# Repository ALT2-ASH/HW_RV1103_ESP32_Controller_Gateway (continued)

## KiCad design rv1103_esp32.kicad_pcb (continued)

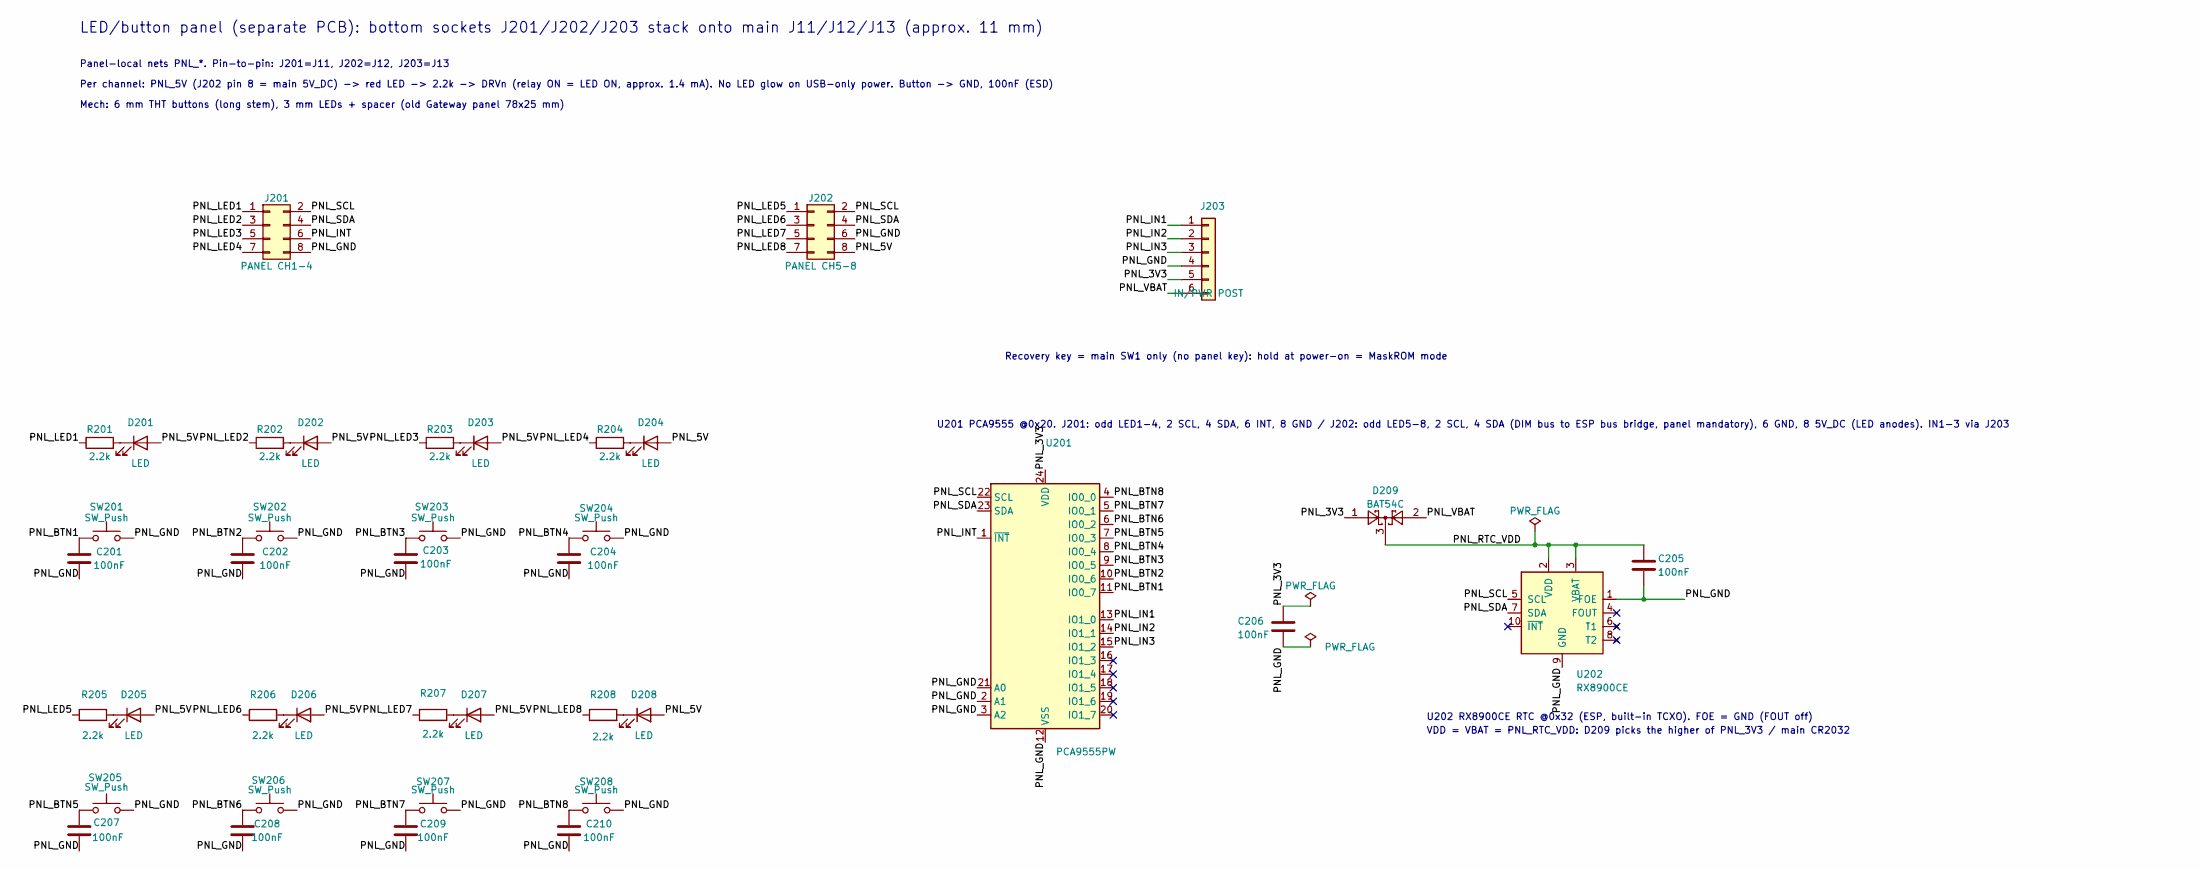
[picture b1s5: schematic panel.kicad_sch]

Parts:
C201, C202, C203, C204, C205, C206, C207, C208, C209, C210: 100nF; C_0603_1608Metric; LCSC C14663
D201, D202, D203, D204, D205, D206, D207, D208: LED; LED_D3.0mm; MPN 204-10SURD/S530-A3-L; LCSC C99771
D209: BAT54C; SOT-23; MPN BAT54C,215; LCSC C37704
J201: PANEL CH1-4; PinSocket_2x04_P2.54mm_Vertical; MPN PM254V-12-08-H85; LCSC C55223345
J202: PANEL CH5-8; PinSocket_2x04_P2.54mm_Vertical; MPN PM254V-12-08-H85; LCSC C55223345
J203: IN/PWR POST; PinSocket_1x06_P2.54mm_Vertical; MPN PM254V-11-06-H85; LCSC C2832269
R201, R202, R203, R204, R205, R206, R207, R208: 2.2k; R_0603_1608Metric; LCSC C4190
SW201, SW202, SW203, SW204, SW205, SW206, SW207, SW208: SW_Push; SW_PUSH_6mm_H8mm; MPN TC-6610-17-260G; LCSC C2845266
U201: PCA9555PW; TSSOP-24_4.4x7.8mm_P0.65mm; MPN PCA9555PW,118; LCSC C128392
U202: RX8900CE; EPSON_CE-USON-10_USON-10_3.2x2.5mm_P0.7mm; MPN RX8900CE-NF; LCSC C54946598

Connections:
/Panel/PNL_3V3: C206.1, D209.1, J203.5, U201.24 (VDD)
/Panel/PNL_5V: D201.2 (A), D202.2 (A), D203.2 (A), D204.2 (A), D205.2 (A), D206.2 (A), D207.2 (A), D208.2 (A), J202.8
/Panel/PNL_BTN1: C201.1, SW201.1, U201.11 (IO0_7)
/Panel/PNL_BTN2: C202.1, SW202.1, U201.10 (IO0_6)
/Panel/PNL_BTN3: C203.1, SW203.1, U201.9 (IO0_5)
/Panel/PNL_BTN4: C204.1, SW204.1, U201.8 (IO0_4)
/Panel/PNL_BTN5: C207.1, SW205.1, U201.7 (IO0_3)
/Panel/PNL_BTN6: C208.1, SW206.1, U201.6 (IO0_2)
/Panel/PNL_BTN7: C209.1, SW207.1, U201.5 (IO0_1)
/Panel/PNL_BTN8: C210.1, SW208.1, U201.4 (IO0_0)
/Panel/PNL_GND: C201.2, C202.2, C203.2, C204.2, C205.2, C206.2, C207.2, C208.2, C209.2, C210.2, J201.8, J202.6, J203.4, SW201.2, SW202.2, SW203.2, SW204.2, SW205.2, SW206.2, SW207.2, SW208.2, U201.2 (A1), U201.3 (A2), U201.12 (VSS), U201.21 (A0), U202.1 (FOE), U202.9 (GND)
/Panel/PNL_IN1: J203.1, U201.13 (IO1_0)
/Panel/PNL_IN2: J203.2, U201.14 (IO1_1)
/Panel/PNL_IN3: J203.3, U201.15 (IO1_2)
/Panel/PNL_INT: J201.6, U201.1 (~INT)
/Panel/PNL_LED1: J201.1, R201.1
/Panel/PNL_LED2: J201.3, R202.1
/Panel/PNL_LED3: J201.5, R203.1
/Panel/PNL_LED4: J201.7, R204.1
/Panel/PNL_LED5: J202.1, R205.1
/Panel/PNL_LED6: J202.3, R206.1
/Panel/PNL_LED7: J202.5, R207.1
/Panel/PNL_LED8: J202.7, R208.1
/Panel/PNL_RTC_VDD: C205.1, D209.3, U202.2 (VDD), U202.3 (VBAT)
/Panel/PNL_SCL: J201.2, J202.2, U201.22 (SCL), U202.5 (SCL)
/Panel/PNL_SDA: J201.4, J202.4, U201.23 (SDA), U202.7 (SDA)
/Panel/PNL_VBAT: D209.2, J203.6
unnamed: D201.1 (K), R201.2
unnamed: D202.1 (K), R202.2
unnamed: D203.1 (K), R203.2
unnamed: D204.1 (K), R204.2
unnamed: D205.1 (K), R205.2
unnamed: D206.1 (K), R206.2
unnamed: D207.1 (K), R207.2
unnamed: D208.1 (K), R208.2

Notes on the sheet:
U202 RX8900CE RTC @0x32 (ESP, built-in TCXO). FOE = GND (FOUT off)
VDD = VBAT = PNL_RTC_VDD: D209 picks the higher of PNL_3V3 / main CR2032
U201 PCA9555 @0x20. J201: odd LED1-4, 2 SCL, 4 SDA, 6 INT, 8 GND / J202: odd LED5-8, 2 SCL, 4 SDA (DIM bus to ESP bus bridge, panel mandatory), 6 GND, 8 5V_DC (LED anodes). IN1-3 via J203
Mech: 6 mm THT buttons (long stem), 3 mm LEDs + spacer (old Gateway panel 78x25 mm)
LED/button panel (separate PCB): bottom sockets J201/J202/J203 stack onto main J11/J12/J13 (approx. 11 mm)
Recovery key = main SW1 only (no panel key): hold at power-on = MaskROM mode
Panel-local nets PNL_*. Pin-to-pin: J201=J11, J202=J12, J203=J13
Per channel: PNL_5V (J202 pin 8 = main 5V_DC) -> red LED -> 2.2k -> DRVn (relay ON = LED ON, approx. 1.4 mA). No LED glow on USB-only power. Button -> GND, 100nF (ESD)

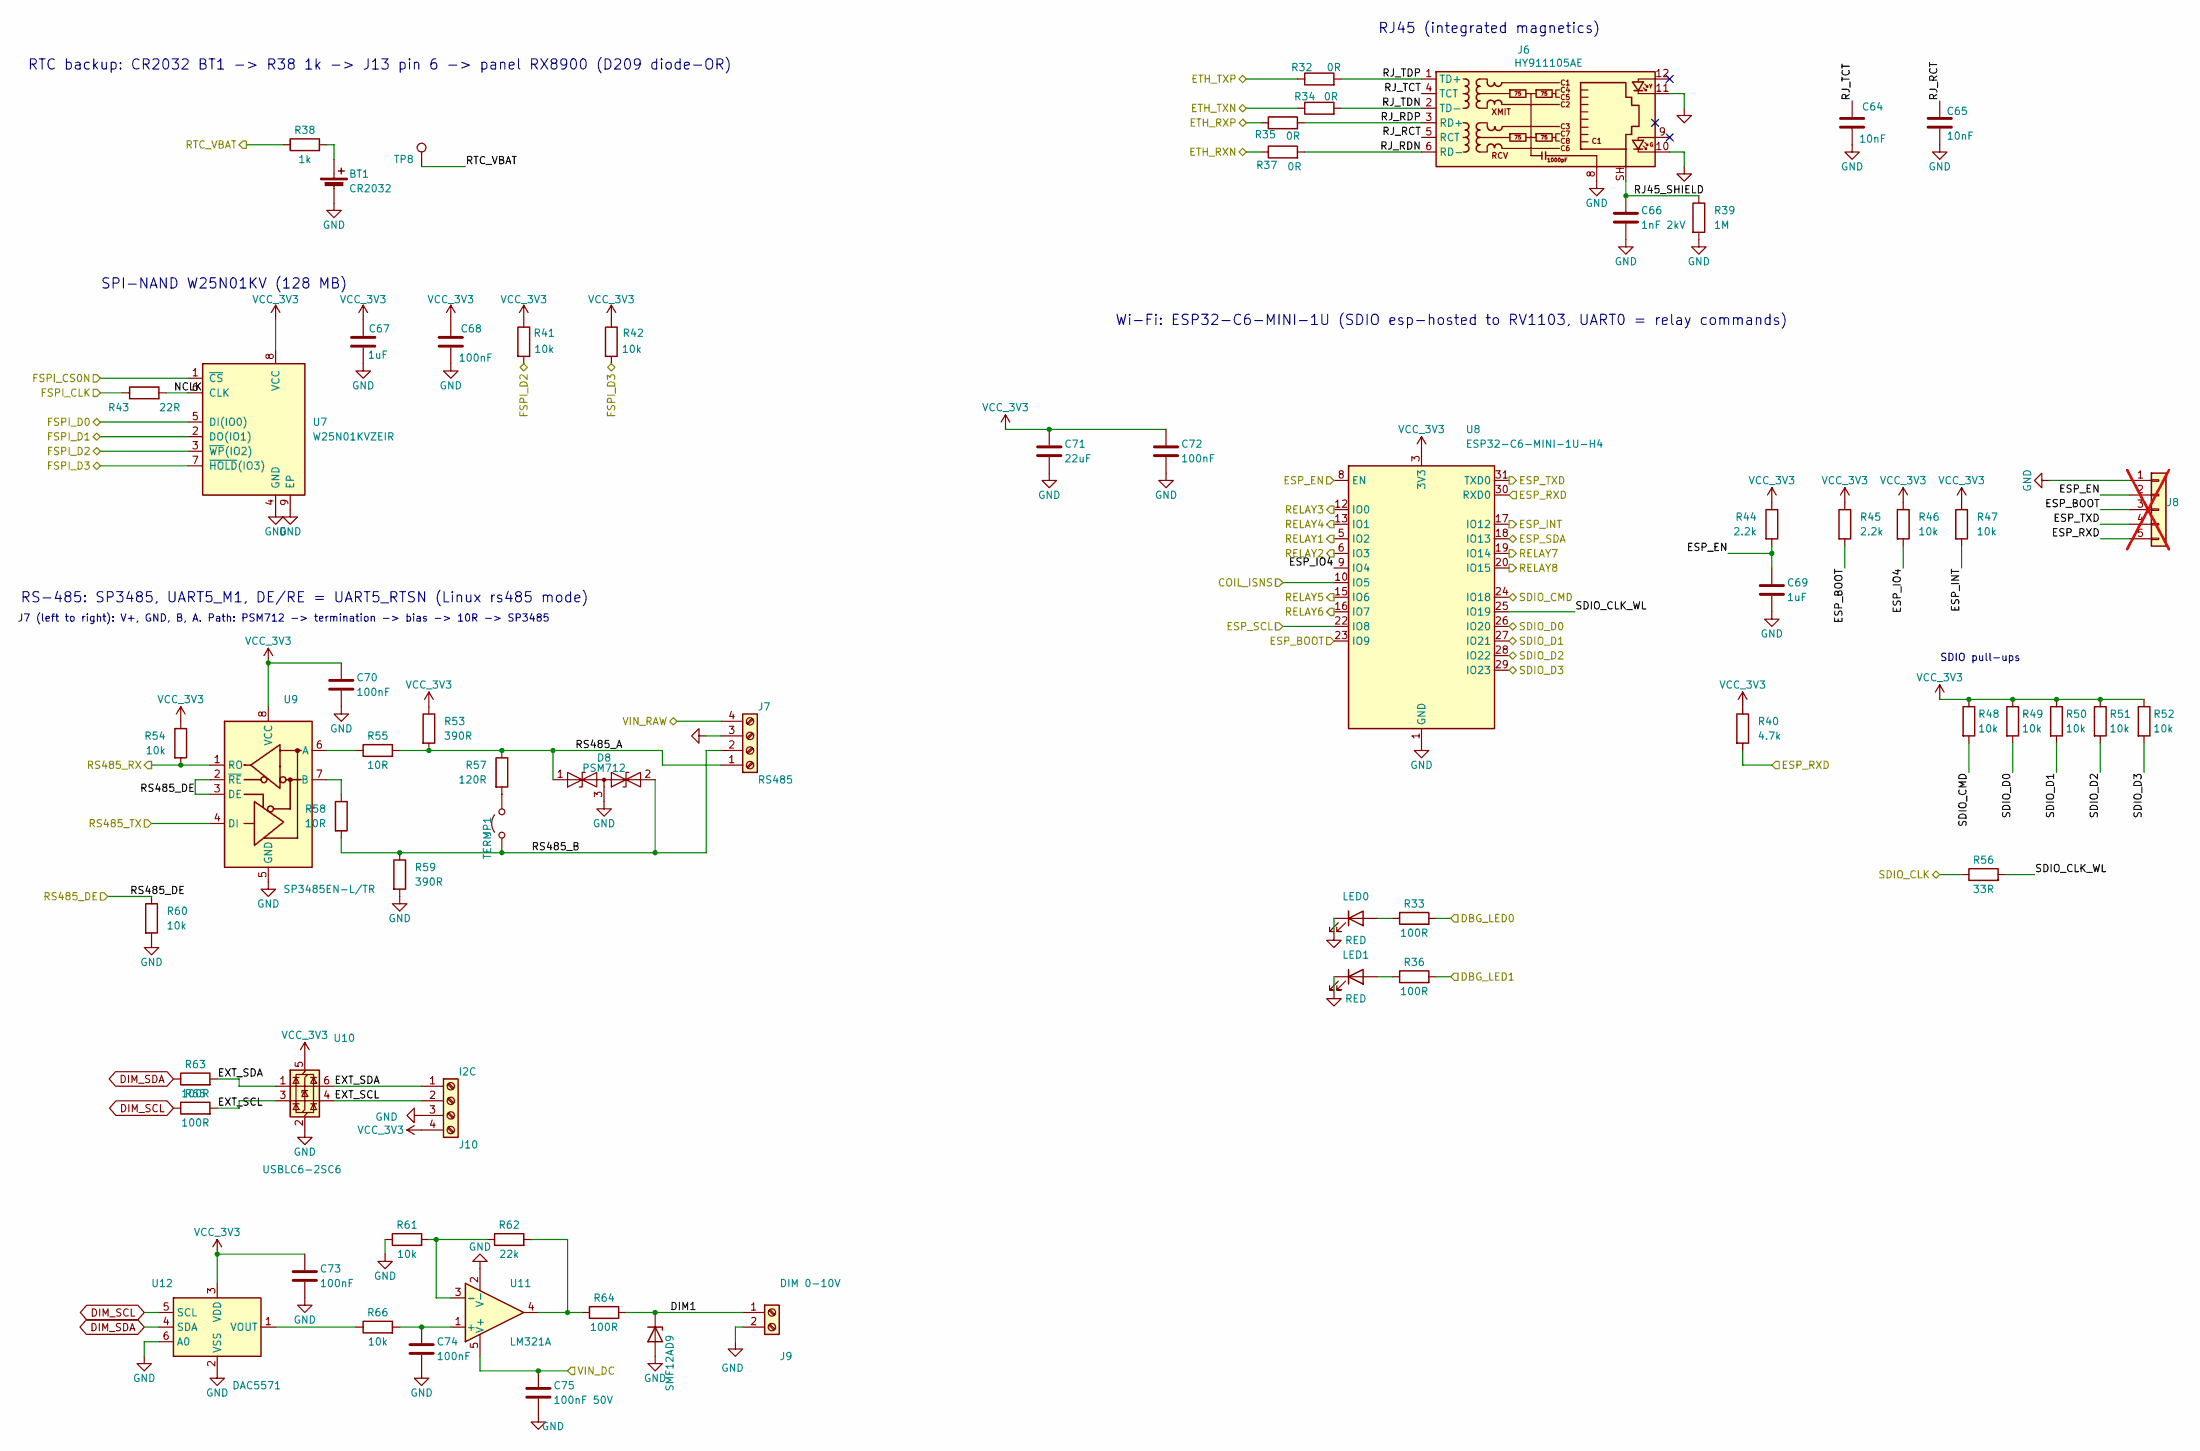
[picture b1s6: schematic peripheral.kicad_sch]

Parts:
BT1: CR2032; BatteryHolder_MYOUNG_BS-05_CR2032_Vertical_Overhang; MPN BS-05-A1BK017; LCSC C2902326
C64, C65: 10nF; C_0402_1005Metric; LCSC C15195
C66: 1nF 2kV; C_1206_3216Metric; Voltage 2kV; LCSC C9196
C67, C69: 1uF; C_0402_1005Metric; LCSC C52923
C68, C70, C72, C73, C74: 100nF; C_0402_1005Metric; LCSC C1525
C71: 22uF; C_0603_1608Metric; LCSC C59461
C75: 100nF 50V; C_0603_1608Metric; LCSC C14663
D8: PSM712; SOT-23; MPN PSM712-LF-T7; LCSC C32677
D9: SMF12A; D_SOD-123F; LCSC C19077506
J6: HY911105AE; RJ45_Hanrun_HY911105AE_Horizontal; LCSC C69427
J7: RS485; TerminalBlock_DB127V-5.0_1x04_P5.00mm; MPN DB127V-5.0-4P-GN-S; LCSC C430624
J8: ESP32 DEBUG; PinHeader_1x05_P2.54mm_Vertical; not fitted
J9: DIM 0-10V; TerminalBlock_DB127V-5.0_1x02_P5.00mm; MPN DB127V-5.0-2P-GN-S; LCSC C395885
J10: I2C; TerminalBlock_DB127V-5.0_1x04_P5.00mm; MPN DB127V-5.0-4P-GN-S; LCSC C430624
JP1: TERM; SolderJumper-2_P1.3mm_Open_RoundedPad1.0x1.5mm
LED0, LED1: RED; LED_0603_1608Metric; MPN KT-0603R; LCSC C2286
R32, R34, R35, R37: 0R; R_0402_1005Metric; LCSC C17168
R33, R36, R63, R64, R65: 100R; R_0402_1005Metric; LCSC C25076
R38: 1k; R_0402_1005Metric; LCSC C11702
R39: 1M; R_0402_1005Metric; LCSC C26083
R40: 4.7k; R_0402_1005Metric; LCSC C25900
R41, R42, R46, R47, R48, R49, R50, R51, R52, R54, R60, R61, R66: 10k; R_0402_1005Metric; LCSC C25744
R43: 22R; R_0402_1005Metric; LCSC C25092
R44, R45: 2.2k; R_0402_1005Metric; LCSC C25879
R53, R59: 390R; R_0603_1608Metric; MPN 0603WAF3900T5E; LCSC C23151
R55, R58: 10R; R_0805_2012Metric; LCSC C17415
R56: 33R; R_0402_1005Metric; LCSC C25105
R57: 120R; R_0603_1608Metric; LCSC C22787
R62: 22k; R_0402_1005Metric; LCSC C25768
TP8: RTC_VDD; TestPoint_Pad_D1.5mm
U7: W25N01KVZEIR; WSON-8-1EP_8x6mm_P1.27mm_EP3.4x4.3mm_HandSolder; MPN W25N01KVZEIR; LCSC C22472329
U8: ESP32-C6-MINI-1U-H4; ESP32-C6-MINI-1U; MPN ESP32-C6-MINI-1U-H4; LCSC C20627095
U9: SP3485EN-L/TR; SOIC-8_3.9x4.9mm_P1.27mm; MPN SP3485EN-L/TR; LCSC C8963
U10: USBLC6-2SC6; SOT-23-6; LCSC C7519
U11: LM321A; SOT-23-5; MPN LM321A-TR; LCSC C2842352
U12: DAC5571; SOT-23-6; MPN DAC5571IDBVR; LCSC C24061

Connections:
/COIL_ISNS: U8.10 (IO5); also elsewhere on the board
/DBG_LED0: R33.2; also elsewhere on the board
/DBG_LED1: R36.2; also elsewhere on the board
/ESP_BOOT: J8.3, R45.2, U8.23 (IO9); also elsewhere on the board
/ESP_EN: C69.1, J8.2, R44.2, U8.8 (EN); also elsewhere on the board
/ESP_INT: R47.2, U8.17 (IO12); also elsewhere on the board
/ESP_RXD: J8.5, R40.2, U8.30 (RXD0); also elsewhere on the board
/ESP_SCL: U8.22 (IO8); also elsewhere on the board
/ESP_SDA: U8.18 (IO13); also elsewhere on the board
/ESP_TXD: J8.4, U8.31 (TXD0); also elsewhere on the board
/ETH_RXN: R37.1; also elsewhere on the board
/ETH_RXP: R35.1; also elsewhere on the board
/ETH_TXN: R34.1; also elsewhere on the board
/ETH_TXP: R32.1; also elsewhere on the board
/FSPI_CLK: R43.1; also elsewhere on the board
/FSPI_CS0N: U7.1 (~CS); also elsewhere on the board
/FSPI_D0: U7.5 (DI(IO0)); also elsewhere on the board
/FSPI_D1: U7.2 (DO(IO1)); also elsewhere on the board
/FSPI_D2: R41.2, U7.3 (~WP(IO2)); also elsewhere on the board
/FSPI_D3: R42.2, U7.7 (~HOLD(IO3)); also elsewhere on the board
/Peripheral/DIM1: D9.1 (K), J9.1, R64.2
/Peripheral/ESP_IO4: R46.2, U8.9 (IO4)
/Peripheral/EXT_SCL: J10.2, R65.2, U10.3 (I/O2), U10.4 (I/O2)
/Peripheral/EXT_SDA: J10.1, R63.2, U10.1 (I/O1), U10.6 (I/O1)
/Peripheral/NCLK: R43.2, U7.6 (CLK)
/Peripheral/RJ45_SHIELD: C66.1, J6.SH, R39.1
/Peripheral/RJ_RCT: C65.1, J6.5 (RCT)
/Peripheral/RJ_RDN: J6.6 (RD-), R37.2
/Peripheral/RJ_RDP: J6.3 (RD+), R35.2
/Peripheral/RJ_TCT: C64.1, J6.4 (TCT)
/Peripheral/RJ_TDN: J6.2 (TD-), R34.2
/Peripheral/RJ_TDP: J6.1 (TD+), R32.2
/Peripheral/RS485_A: D8.1 (A1), J7.1, R53.2, R55.2, R57.1
/Peripheral/RS485_B: D8.2 (A2), J7.2, JP1.1 (A), R58.2, R59.1
/Peripheral/SDIO_CLK_WL: R56.2, U8.25 (IO19)
/RELAY1: U8.5 (IO2); also elsewhere on the board
/RELAY2: U8.6 (IO3); also elsewhere on the board
/RELAY3: U8.12 (IO0); also elsewhere on the board
/RELAY4: U8.13 (IO1); also elsewhere on the board
/RELAY5: U8.15 (IO6); also elsewhere on the board
/RELAY6: U8.16 (IO7); also elsewhere on the board
/RELAY7: U8.19 (IO14); also elsewhere on the board
/RELAY8: U8.20 (IO15); also elsewhere on the board
/RS485_DE: R60.1, U9.2 (~RE), U9.3 (DE); also elsewhere on the board
/RS485_RX: R54.2, U9.1 (RO); also elsewhere on the board
/RS485_TX: U9.4 (DI); also elsewhere on the board
/RTC_VBAT: R38.1, TP8.1 (1_1); also elsewhere on the board
/SDIO_CLK: R56.1; also elsewhere on the board
/SDIO_CMD: R48.2, U8.24 (IO18); also elsewhere on the board
/SDIO_D0: R49.2, U8.26 (IO20); also elsewhere on the board
/SDIO_D1: R50.2, U8.27 (IO21); also elsewhere on the board
/SDIO_D2: R51.2, U8.28 (IO22); also elsewhere on the board
/SDIO_D3: R52.2, U8.29 (IO23); also elsewhere on the board
/VIN_DC: C75.1, U11.5 (V+); also elsewhere on the board
/VIN_RAW: J7.4; also elsewhere on the board
DIM_SCL: R65.1, U12.5 (SCL); also elsewhere on the board
DIM_SDA: R63.1, U12.4 (SDA); also elsewhere on the board
GND: BT1.2 (-), C64.2, C65.2, C66.2, C67.2, C68.2, C69.2, C70.2, C71.2, C72.2, C73.2, C74.2, C75.2, D8.3 (common), D9.2 (A), J6.8, J6.10, J6.11, J7.3, J8.1, J9.2, J10.3, LED0.1 (K), LED1.1 (K), R39.2, R59.2, R60.2, R61.1, U7.4 (GND), U7.9 (EP), U8.1 (GND), U8.2 (GND), U8.11 (GND), U8.14 (GND), U8.36 (GND), U8.37 (GND), U8.38 (GND), U8.39 (GND), U8.40 (GND), U8.41 (GND), U8.42 (GND), U8.43 (GND), U8.44 (GND), U8.45 (GND), U8.46 (GND), U8.47 (GND), U8.48 (GND), U8.49 (GND), U8.50 (GND), U8.51 (GND), U8.52 (GND), U8.53 (GND), U9.5 (GND), U10.2 (GND), U11.2 (V-), U12.2 (VSS), U12.6 (A0); also elsewhere on the board
unnamed: BT1.1 (+), R38.2
unnamed: JP1.2 (B), R57.2
unnamed: LED0.2 (A), R33.1
unnamed: LED1.2 (A), R36.1
unnamed: R62.2, R64.1, U11.4
unnamed: R55.1, U9.6 (A)
unnamed: R58.1, U9.7 (B)
unnamed: C74.1, R66.2, U11.1 (+)
unnamed: R61.2, R62.1, U11.3 (-)
unnamed: R66.1, U12.1 (VOUT)
VCC_3V3: C67.1, C68.1, C70.1, C71.1, C72.1, C73.1, J10.4, R40.1, R41.1, R42.1, R44.1, R45.1, R46.1, R47.1, R48.1, R49.1, R50.1, R51.1, R52.1, R53.1, R54.1, U7.8 (VCC), U8.3 (3V3), U9.8 (VCC), U10.5 (VBUS), U12.3 (VDD); also elsewhere on the board

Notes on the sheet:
RTC backup: CR2032 BT1 -> R38 1k -> J13 pin 6 -> panel RX8900 (D209 diode-OR)
Wi-Fi: ESP32-C6-MINI-1U (SDIO esp-hosted to RV1103, UART0 = relay commands)
J7 (left to right): V+, GND, B, A. Path: PSM712 -> termination -> bias -> 10R -> SP3485
SDIO pull-ups
RJ45 (integrated magnetics)
RS-485: SP3485, UART5_M1, DE/RE = UART5_RTSN (Linux rs485 mode)
SPI-NAND W25N01KV (128 MB)

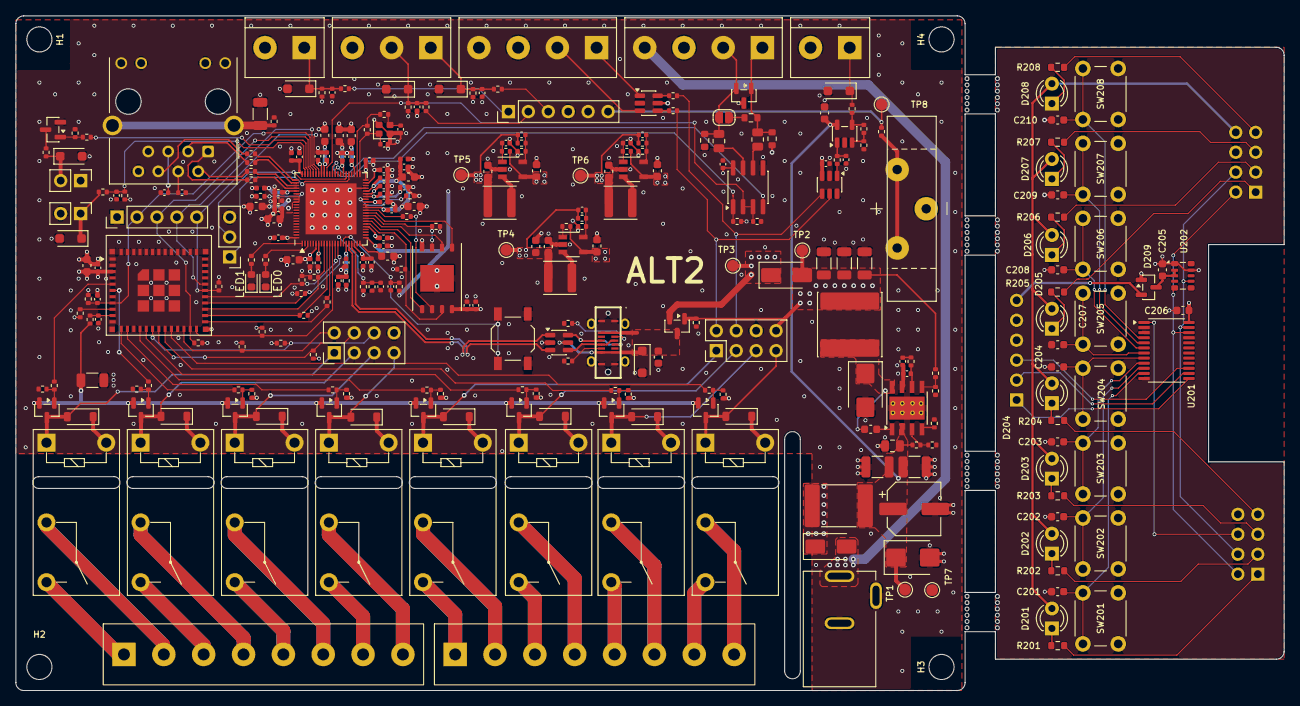
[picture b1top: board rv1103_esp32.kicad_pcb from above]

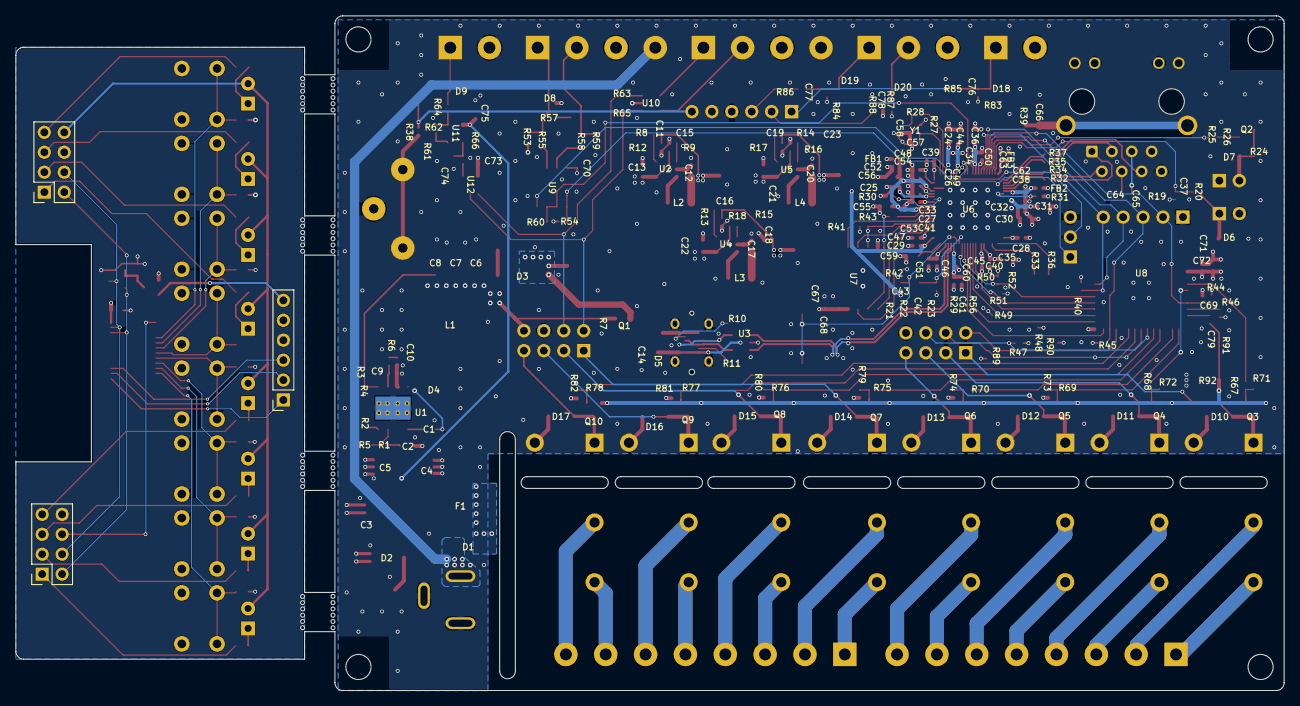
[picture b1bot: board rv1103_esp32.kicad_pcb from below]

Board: 4 copper layers, 161.7 x 86.0 mm, 308 parts (3 on the bottom side), 189 nets.

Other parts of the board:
MB1, MB2, MB3, MB4: MouseBite; MouseBite_5mm_Gap3.873mm

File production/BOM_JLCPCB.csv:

Comment,Designator,Footprint,JLCPCB Part #
CR2032,BT1,BatteryHolder_MYOUNG_BS-05_CR2032_Vertical_Overhang,C2902326
100nF / 100nF 50V,"C1,C75,C201,C202,C203,C204,C205,C206,C207,C208,C209,C210",C_0603_1608Metric,C14663
100nF,C2,C_0805_2012Metric,C28233
33uF,C3,CP_Elec_6.3x7.7,C402500
2.2uF,"C4,C5",C_1210_3225Metric,C42400139
47uF,"C6,C7,C8",C_1206_3216Metric,C96123
47pF,C9,C_0402_1005Metric,C1567
6.8nF,C10,C_0402_1005Metric,C1542
22pF,C11,C_0402_1005Metric,C1555
22uF,"C12,C17,C18,C20,C71",C_0603_1608Metric,C59461
10uF,"C13,C21,C22,C24,C30,C31,C35,C36,C44,C55,C56",C_0603_1608Metric,C19702
2.2uF,C14,C_0603_1608Metric,C23630
100nF,"C15,C23,C26,C27,C28,C29,C37,C38,C39,C40,C41,C42,C45,C46,C47,C48,C49,C50,C51,C53,C54,C60,C62,C63,C68,C70,C72,C73,C74,C76,C77,C78,C79",C_0402_1005Metric,C1525
6.8pF,"C16,C19",C_0402_1005Metric,C1576
1uF,"C25,C32,C33,C34,C52,C61,C67,C69",C_0402_1005Metric,C52923
1nF,C43,C_0402_1005Metric,C1523
18pF,"C57,C58",C_0402_1005Metric,C1549
4.7uF,C59,C_0603_1608Metric,C19666
10nF,"C64,C65",C_0402_1005Metric,C15195
1nF 2kV,C66,C_1206_3216Metric,C9196
SS510,D1,D_SMA,C65010
SMBJ33A,D2,D_SMB,C78419
SS54,D3,D_SMA,C22452
SS56B,D4,D_SMB,C18199180
SMF5.0A,"D5,D6,D7,D18,D19,D20",D_SOD-123F,C2759874
PSM712,D8,SOT-23,C32677
SMF12A,D9,D_SOD-123F,C19077506
1N4148W,"D10,D11,D12,D13,D14,D15,D16,D17",D_SOD-123,C81598
LED,"D201,D202,D203,D204,D205,D206,D207,D208",LED_D3.0mm,C99771
BAT54C,D209,SOT-23,C37704
PTC 2.5A 48V,F1,Fuse_2920_7451Metric,C49326264
BLM15PD121SN1D,"FB1,FB2,FB3",L_0402_1005Metric,C76891
DC 12-24V,J1,DC-005-A200_XUNPU_Horizontal,C720557
USB_C_Receptacle_USB2.0_16P,J2,USB_C_Receptacle_HRO_TYPE-C-31-D-06_Vertical,C22464422
FRONT_BTN / FRONT_LED,"J4,J5",PinHeader_1x02_P2.54mm_Vertical,C492401
HY911105AE,J6,RJ45_Hanrun_HY911105AE_Horizontal,C69427
RS485 / I2C,"J7,J10",TerminalBlock_DB127V-5.0_1x04_P5.00mm,C430624
DIM 0-10V / IN1,"J9,J15",TerminalBlock_DB127V-5.0_1x02_P5.00mm,C395885
PANEL CH1-4 / PANEL CH5-8,"J11,J12",PinHeader_2x04_P2.54mm_Vertical,C492421
PANEL IN/PWR POST,J13,PinHeader_1x06_P2.54mm_Vertical,C492405
IN2-3,J14,TerminalBlock_DB127V-5.0_1x03_P5.00mm,C395886
RELAY 1-4 / RELAY 5-8,"J16,J17",TerminalBlock_bornier-8_P5.08mm,C5143711
G5Q-1A4 DC5,"K1,K2,K3,K4,K5,K6,K7,K8",Relay_SPST_Omron-G5Q-1A,C5204063
8.2uH,L1,L_Sunlord_SWPA8065S,C168161
2.2uH,"L2,L3,L4",L_Sunlord_SWPA4030S,C279948
RED,"LED0,LED1",LED_0603_1608Metric,C2286
AO3401A,Q1,SOT-23,C15127
AO3400A,"Q2,Q3,Q4,Q5,Q6,Q7,Q8,Q9,Q10",SOT-23,C20917
470k,R1,R_0402_1005Metric,C25790
150k,"R2,R8",R_0402_1005Metric,C25755
100k,"R3,R16,R17,R18,R22,R23",R_0402_1005Metric,C25741
18k,R4,R_0402_1005Metric,C25762
75k,R5,R_0402_1005Metric,C25798
12k,R6,R_0402_1005Metric,C25752
10k,"R7,R15,R21,R26,R41,R42,R46,R47,R48,R49,R50,R51,R52,R54,R60,R61,R66",R_0402_1005Metric,C25744
200k,"R9,R14",R_0402_1005Metric,C25764
5.1k,"R10,R11",R_0402_1005Metric,C25905
33k,R12,R_0402_1005Metric,C25779
51k,R13,R_0402_1005Metric,C25794
4.7k,"R19,R40,R83,R84,R87,R89,R90",R_0402_1005Metric,C25900
100R,"R20,R25,R33,R36,R63,R64,R65,R67,R68,R69,R70,R75,R76,R77,R78",R_0402_1005Metric,C25076
330R,R24,R_0402_1005Metric,C25104
1M,"R27,R39",R_0402_1005Metric,C26083
22R,"R28,R43",R_0402_1005Metric,C25092
1R,R29,R_0402_1005Metric,C25086
240R,R30,R_0402_1005Metric,C114755
6.04k,R31,R_0402_1005Metric,C97819
0R,"R32,R34,R35,R37",R_0402_1005Metric,C17168
1k,"R38,R85,R86,R88,R91",R_0402_1005Metric,C11702
2.2k,"R44,R45,R71,R72,R73,R74,R79,R80,R81,R82",R_0402_1005Metric,C25879
390R,"R53,R59",R_0603_1608Metric,C23151
10R,"R55,R58",R_0805_2012Metric,C17415
33R,R56,R_0402_1005Metric,C25105
120R,R57,R_0603_1608Metric,C22787
22k,R62,R_0402_1005Metric,C25768
0.47R,R92,R_1206_3216Metric,C327076
2.2k,"R201,R202,R203,R204,R205,R206,R207,R208",R_0603_1608Metric,C4190
RECOVERY,SW1,SW_SPST_TL3342,C318884
SW_Push,"SW201,SW202,SW203,SW204,SW205,SW206,SW207,SW208",SW_PUSH_6mm_H8mm,C2845266
TPS54360BDDAR,U1,TI_SO-PowerPAD-8_ThermalVias,C524806
TLV62569DBVR,"U2,U4,U5",SOT-23-5_TI_DBV0005A,C141836
USBLC6-2SC6,"U3,U10",SOT-23-6,C7519
RV1103G1,U6,QFN-88-1EP_9x9mm_P0.35mm_EP6.5x6.5mm,C5307358
W25N01KVZEIR,U7,WSON-8-1EP_8x6mm_P1.27mm_EP3.4x4.3mm_HandSolder,C22472329
ESP32-C6-MINI-1U-H4,U8,ESP32-C6-MINI-1U,C20627095
SP3485EN-L/TR,U9,SOIC-8_3.9x4.9mm_P1.27mm,C8963
LM321A,U11,SOT-23-5,C2842352
DAC5571,U12,SOT-23-6,C24061
PCA9555PW,U201,TSSOP-24_4.4x7.8mm_P0.65mm,C128392
RX8900CE,U202,EPSON_CE-USON-10_USON-10_3.2x2.5mm_P0.7mm,C54946598
24MHz,Y1,Crystal_SMD_2016-4Pin_2.0x1.6mm,C5261099
LED spacer 4x10mm,"SP201,SP202,SP203,SP204,SP205,SP206,SP207,SP208",LED_Spacer_4x10mm,C94096
